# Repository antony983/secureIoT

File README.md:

# secureIoT
sample secureIOT design

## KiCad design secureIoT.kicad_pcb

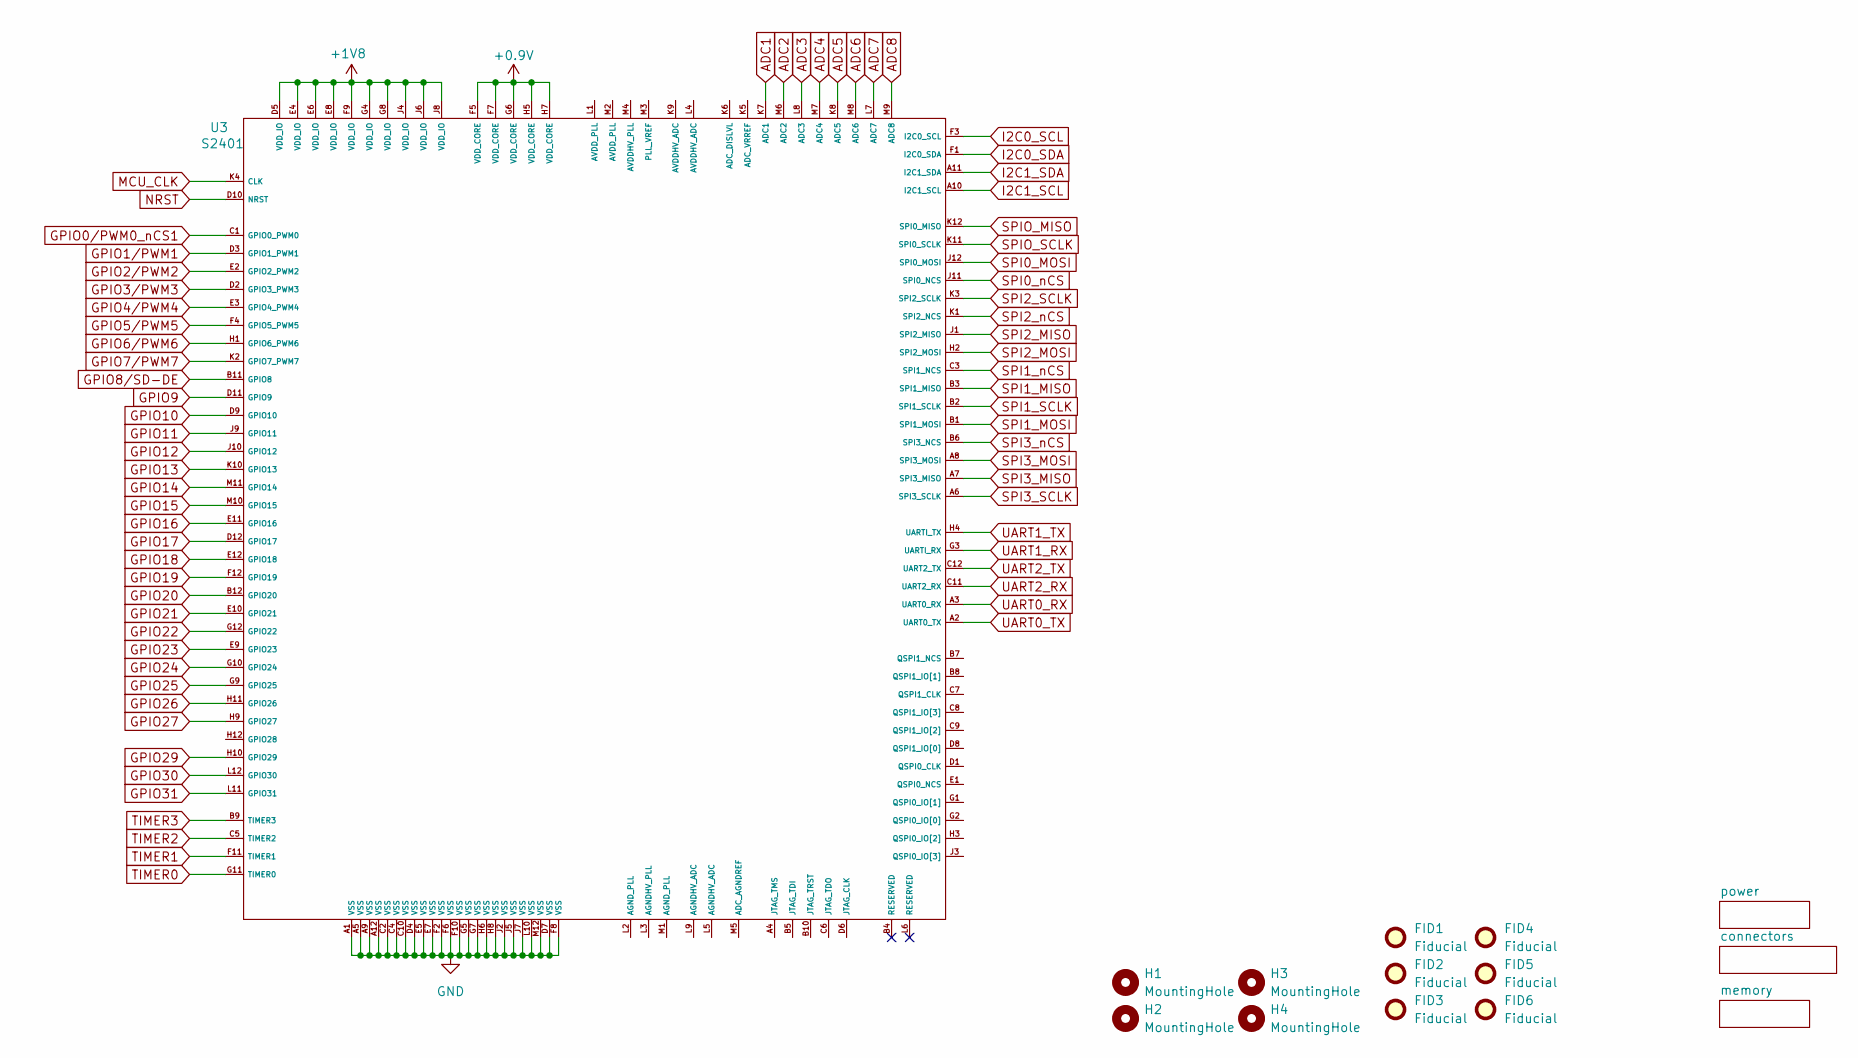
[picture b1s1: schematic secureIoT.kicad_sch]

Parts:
FID1, FID2, FID3, FID4, FID5, FID6: Fiducial; Fiducial_0.5mm_Mask1mm
H1, H2, H3, H4: MountingHole; MountingHole_3.5mm
U3: S2401; S4201

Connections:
+0.9V: U3.F5 (VDD_CORE), U3.F7 (VDD_CORE), U3.G6 (VDD_CORE), U3.H5 (VDD_CORE), U3.H7 (VDD_CORE); also elsewhere on the board
+1V8: U3.D5 (VDD_IO), U3.E4 (VDD_IO), U3.E6 (VDD_IO), U3.E8 (VDD_IO), U3.F9 (VDD_IO), U3.G4 (VDD_IO), U3.G8 (VDD_IO), U3.J4 (VDD_IO), U3.J6 (VDD_IO), U3.J8 (VDD_IO); also elsewhere on the board
ADC1: U3.K7 (ADC1); also elsewhere on the board
ADC2: U3.M6 (ADC2); also elsewhere on the board
ADC3: U3.L8 (ADC3); also elsewhere on the board
ADC4: U3.M7 (ADC4); also elsewhere on the board
ADC5: U3.K8 (ADC5); also elsewhere on the board
ADC6: U3.M8 (ADC6); also elsewhere on the board
ADC7: U3.L7 (ADC7); also elsewhere on the board
ADC8: U3.M9 (ADC8); also elsewhere on the board
GND: U3.A1 (VSS), U3.A5 (VSS), U3.A9 (VSS), U3.A12 (VSS), U3.C2 (VSS), U3.C4 (VSS), U3.C10 (VSS), U3.D4 (VSS), U3.D7 (VSS), U3.E5 (VSS), U3.E7 (VSS), U3.F2 (VSS), U3.F6 (VSS), U3.F8 (VSS), U3.F10 (VSS), U3.G5 (VSS), U3.G7 (VSS), U3.H6 (VSS), U3.H8 (VSS), U3.J2 (VSS), U3.J5 (VSS), U3.J7 (VSS), U3.L10 (VSS), U3.M12 (VSS); also elsewhere on the board
GPIO0/PWM0_nCS1: U3.C1 (GPIO0_PWM0); also elsewhere on the board
GPIO1/PWM1: U3.D3 (GPIO1_PWM1); also elsewhere on the board
GPIO2/PWM2: U3.E2 (GPIO2_PWM2); also elsewhere on the board
GPIO3/PWM3: U3.D2 (GPIO3_PWM3); also elsewhere on the board
GPIO4/PWM4: U3.E3 (GPIO4_PWM4); also elsewhere on the board
GPIO5/PWM5: U3.F4 (GPIO5_PWM5); also elsewhere on the board
GPIO6/PWM6: U3.H1 (GPIO6_PWM6); also elsewhere on the board
GPIO7/PWM7: U3.K2 (GPIO7_PWM7); also elsewhere on the board
GPIO8/SD-DE: U3.B11 (GPIO8); also elsewhere on the board
GPIO9: U3.D11 (GPIO9); also elsewhere on the board
GPIO10: U3.D9 (GPIO10); also elsewhere on the board
GPIO11: U3.J9 (GPIO11); also elsewhere on the board
GPIO12: U3.J10 (GPIO12); also elsewhere on the board
GPIO13: U3.K10 (GPIO13); also elsewhere on the board
GPIO14: U3.M11 (GPIO14); also elsewhere on the board
GPIO15: U3.M10 (GPIO15); also elsewhere on the board
GPIO16: U3.E11 (GPIO16); also elsewhere on the board
GPIO17: U3.D12 (GPIO17); also elsewhere on the board
GPIO18: U3.E12 (GPIO18); also elsewhere on the board
GPIO19: U3.F12 (GPIO19); also elsewhere on the board
GPIO20: U3.B12 (GPIO20); also elsewhere on the board
GPIO21: U3.E10 (GPIO21); also elsewhere on the board
GPIO22: U3.G12 (GPIO22); also elsewhere on the board
GPIO23: U3.E9 (GPIO23); also elsewhere on the board
GPIO24: U3.G10 (GPIO24); also elsewhere on the board
GPIO25: U3.G9 (GPIO25); also elsewhere on the board
GPIO26: U3.H11 (GPIO26); also elsewhere on the board
GPIO27: U3.H9 (GPIO27); also elsewhere on the board
GPIO29: U3.H10 (GPIO29); also elsewhere on the board
GPIO30: U3.L12 (GPIO30); also elsewhere on the board
GPIO31: U3.L11 (GPIO31); also elsewhere on the board
I2C0_SCL: U3.F3 (I2C0_SCL); also elsewhere on the board
I2C0_SDA: U3.F1 (I2C0_SDA); also elsewhere on the board
I2C1_SCL: U3.A10 (I2C1_SCL); also elsewhere on the board
I2C1_SDA: U3.A11 (I2C1_SDA); also elsewhere on the board
MCU_CLK: U3.K4 (CLK); also elsewhere on the board
NRST: U3.D10 (NRST); also elsewhere on the board
SPI0_MOSI: U3.J12 (SPI0_MOSI); also elsewhere on the board
SPI0_nCS: U3.J11 (SPI0_NCS); also elsewhere on the board
SPI1_MISO: U3.B3 (SPI1_MISO); also elsewhere on the board
SPI1_MOSI: U3.B1 (SPI1_MOSI); also elsewhere on the board
SPI1_SCLK: U3.B2 (SPI1_SCLK); also elsewhere on the board
SPI1_nCS: U3.C3 (SPI1_NCS); also elsewhere on the board
SPI2_MISO: U3.J1 (SPI2_MISO); also elsewhere on the board
SPI2_MOSI: U3.H2 (SPI2_MOSI); also elsewhere on the board
SPI2_SCLK: U3.K3 (SPI2_SCLK); also elsewhere on the board
SPI2_nCS: U3.K1 (SPI2_NCS); also elsewhere on the board
SPI3_MISO: U3.A7 (SPI3_MISO); also elsewhere on the board
SPI3_MOSI: U3.A8 (SPI3_MOSI); also elsewhere on the board
SPI3_SCLK: U3.A6 (SPI3_SCLK); also elsewhere on the board
SPI3_nCS: U3.B6 (SPI3_NCS); also elsewhere on the board
SPIO_MISO: U3.K12 (SPI0_MISO); also elsewhere on the board
SPIO_SCLK: U3.K11 (SPI0_SCLK); also elsewhere on the board
TIMER0: U3.G11 (TIMER0); also elsewhere on the board
TIMER1: U3.F11 (TIMER1); also elsewhere on the board
TIMER2: U3.C5 (TIMER2); also elsewhere on the board
TIMER3: U3.B9 (TIMER3); also elsewhere on the board
UART0_RX: U3.A3 (UART0_RX); also elsewhere on the board
UART0_TX: U3.A2 (UART0_TX); also elsewhere on the board
UART1_RX: U3.G3 (UARTI_RX); also elsewhere on the board
UART1_TX: U3.H4 (UARTI_TX); also elsewhere on the board
UART2_RX: U3.C11 (UART2_RX); also elsewhere on the board
UART2_TX: U3.C12 (UART2_TX); also elsewhere on the board

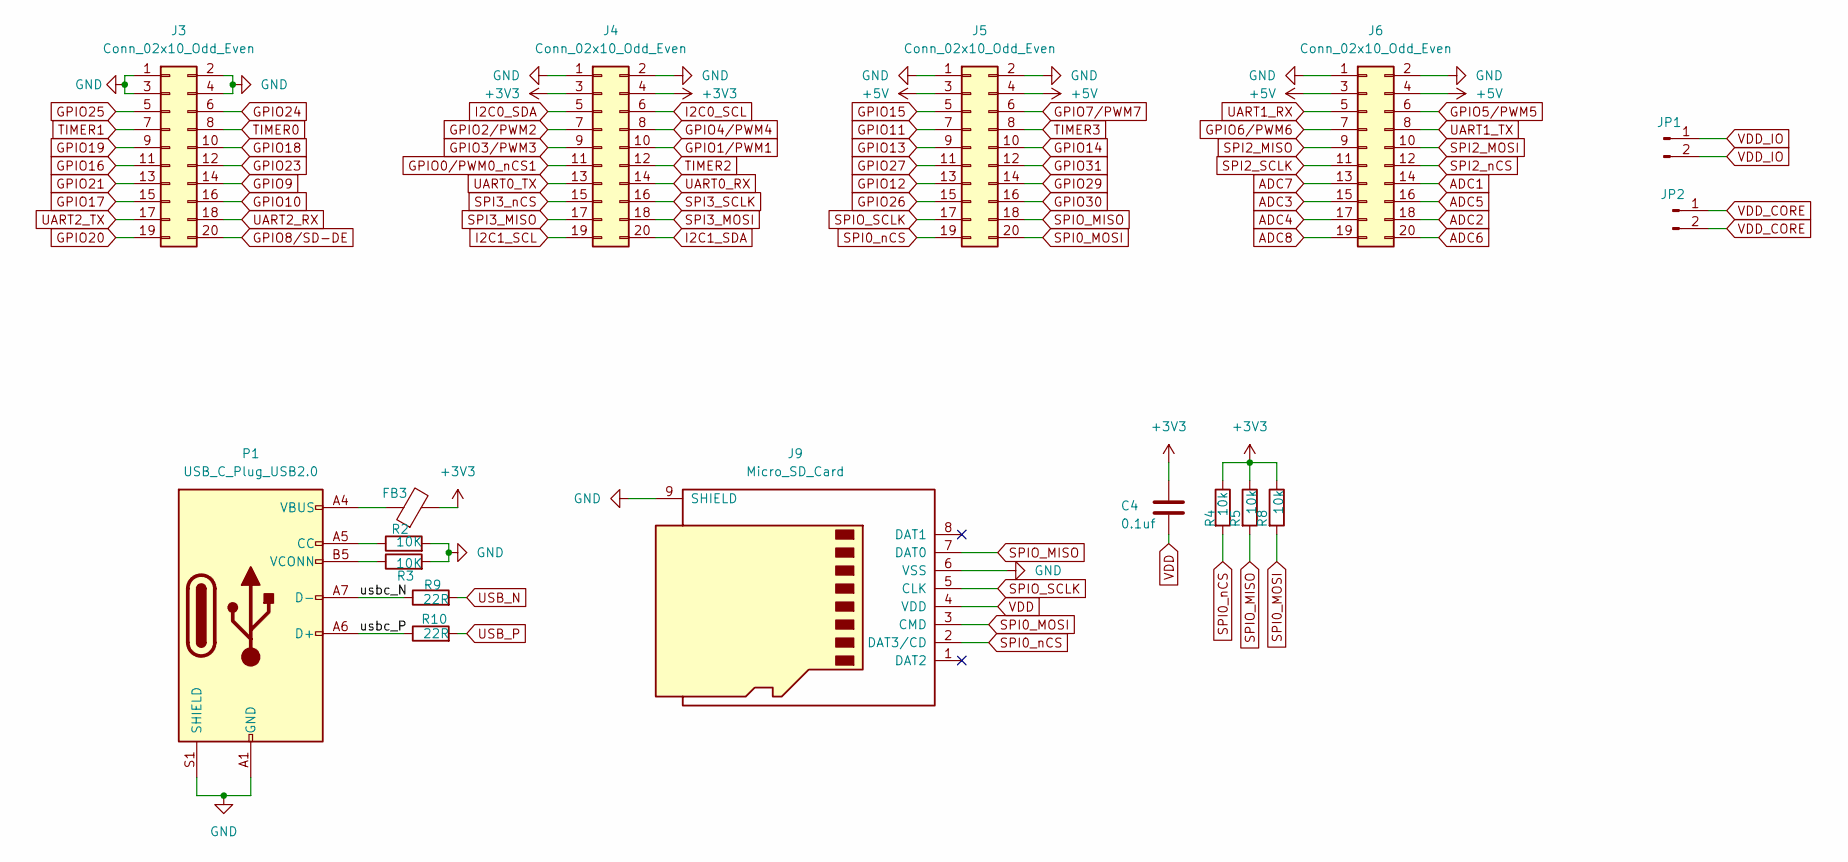
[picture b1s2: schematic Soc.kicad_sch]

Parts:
C4: 0.1uf; C_0603_1608Metric
FB3: FerriteBead; R_0603_1608Metric
J3, J4, J5, J6: Conn_02x10_Odd_Even; PinHeader_2x10_P2.54mm_Vertical
J9: Micro_SD_Card; microSD_HC_Molex_104031-0811
JP1, JP2: Conn_01x02_Pin; PinHeader_1x02_P2.54mm_Vertical
P1: USB_C_Plug_USB2.0; USB_C_Receptacle_GCT_USB4105-xx-A_16P_TopMnt_Horizontal
R2, R3: 10K; R_0603_1608Metric
R4, R5, R8: 10k; R_0603_1608Metric
R9, R10: 22R; R_0603_1608Metric

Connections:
+3V3: C4.1, FB3.2, J4.3, J4.4, R4.1, R5.1, R8.1; also elsewhere on the board
+5V: J5.3, J5.4, J6.3, J6.4; also elsewhere on the board
/connectors/usbc_N: P1.A7 (D-), R9.1
/connectors/usbc_P: P1.A6 (D+), R10.1
ADC1: J6.14; also elsewhere on the board
ADC2: J6.18; also elsewhere on the board
ADC3: J6.15; also elsewhere on the board
ADC4: J6.17; also elsewhere on the board
ADC5: J6.16; also elsewhere on the board
ADC6: J6.20; also elsewhere on the board
ADC7: J6.13; also elsewhere on the board
ADC8: J6.19; also elsewhere on the board
GND: J3.1, J3.2, J3.3, J3.4, J4.1, J4.2, J5.1, J5.2, J6.1, J6.2, J9.6 (VSS), J9.9 (SHIELD), P1.A1 (GND), P1.A12 (GND), P1.B1 (GND), P1.B12 (GND), P1.S1 (SHIELD), R2.2, R3.2; also elsewhere on the board
GPIO0/PWM0_nCS1: J4.11; also elsewhere on the board
GPIO1/PWM1: J4.10; also elsewhere on the board
GPIO2/PWM2: J4.7; also elsewhere on the board
GPIO3/PWM3: J4.9; also elsewhere on the board
GPIO4/PWM4: J4.8; also elsewhere on the board
GPIO5/PWM5: J6.6; also elsewhere on the board
GPIO6/PWM6: J6.7; also elsewhere on the board
GPIO7/PWM7: J5.6; also elsewhere on the board
GPIO8/SD-DE: J3.20; also elsewhere on the board
GPIO9: J3.14; also elsewhere on the board
GPIO10: J3.16; also elsewhere on the board
GPIO11: J5.7; also elsewhere on the board
GPIO12: J5.13; also elsewhere on the board
GPIO13: J5.9; also elsewhere on the board
GPIO14: J5.10; also elsewhere on the board
GPIO15: J5.5; also elsewhere on the board
GPIO16: J3.11; also elsewhere on the board
GPIO17: J3.15; also elsewhere on the board
GPIO18: J3.10; also elsewhere on the board
GPIO19: J3.9; also elsewhere on the board
GPIO20: J3.19; also elsewhere on the board
GPIO21: J3.13; also elsewhere on the board
GPIO23: J3.12; also elsewhere on the board
GPIO24: J3.6; also elsewhere on the board
GPIO25: J3.5; also elsewhere on the board
GPIO26: J5.15; also elsewhere on the board
GPIO27: J5.11; also elsewhere on the board
GPIO29: J5.14; also elsewhere on the board
GPIO30: J5.16; also elsewhere on the board
GPIO31: J5.12; also elsewhere on the board
I2C0_SCL: J4.6; also elsewhere on the board
I2C0_SDA: J4.5; also elsewhere on the board
I2C1_SCL: J4.19; also elsewhere on the board
I2C1_SDA: J4.20; also elsewhere on the board
unnamed: FB3.1, P1.A4 (VBUS), P1.A9 (VBUS), P1.B4 (VBUS), P1.B9 (VBUS)
unnamed: P1.A5 (CC), R2.1
unnamed: P1.B5 (VCONN), R3.1
SPI0_MOSI: J5.20, J9.3 (CMD), R8.2; also elsewhere on the board
SPI0_nCS: J5.19, J9.2 (DAT3/CD), R4.2; also elsewhere on the board
SPI2_MISO: J6.9; also elsewhere on the board
SPI2_MOSI: J6.10; also elsewhere on the board
SPI2_SCLK: J6.11; also elsewhere on the board
SPI2_nCS: J6.12; also elsewhere on the board
SPI3_MISO: J4.17; also elsewhere on the board
SPI3_MOSI: J4.18; also elsewhere on the board
SPI3_SCLK: J4.16; also elsewhere on the board
SPI3_nCS: J4.15; also elsewhere on the board
SPIO_MISO: J5.18, J9.7 (DAT0), R5.2; also elsewhere on the board
SPIO_SCLK: J5.17, J9.5 (CLK); also elsewhere on the board
TIMER0: J3.8; also elsewhere on the board
TIMER1: J3.7; also elsewhere on the board
TIMER2: J4.12; also elsewhere on the board
TIMER3: J5.8; also elsewhere on the board
UART0_RX: J4.14; also elsewhere on the board
UART0_TX: J4.13; also elsewhere on the board
UART1_RX: J6.5; also elsewhere on the board
UART1_TX: J6.8; also elsewhere on the board
UART2_RX: J3.18; also elsewhere on the board
UART2_TX: J3.17; also elsewhere on the board
USB_N: R9.2; also elsewhere on the board
USB_P: R10.2; also elsewhere on the board
VDD: C4.2, J9.4 (VDD)
VDD_CORE: JP2.1, JP2.2
VDD_IO: JP1.1, JP1.2

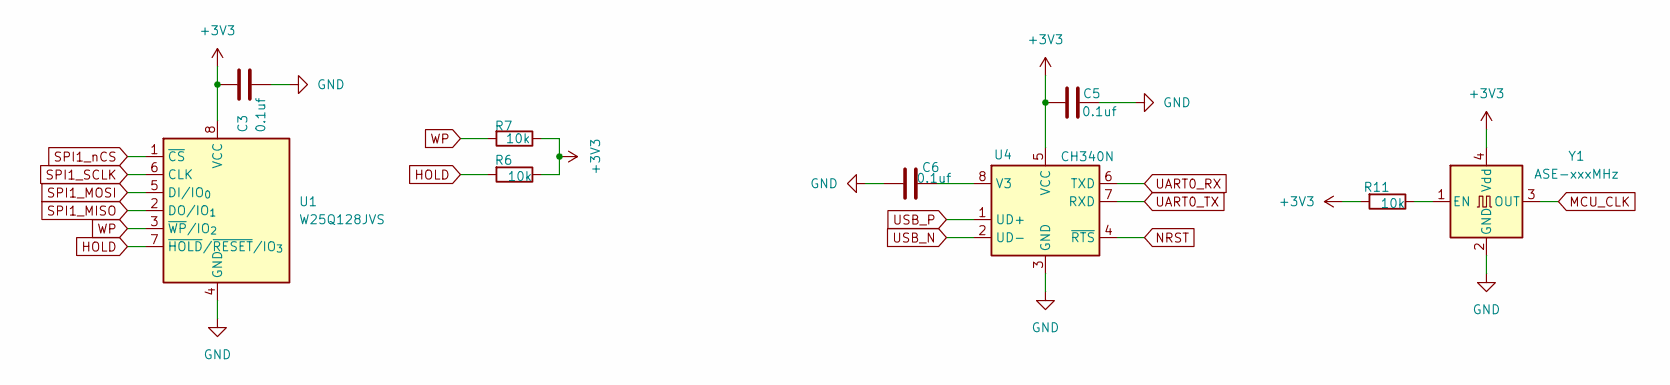
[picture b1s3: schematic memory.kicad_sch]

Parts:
C3, C5, C6: 0.1uf; C_0603_1608Metric
R6, R7, R11: 10k; R_0603_1608Metric
U1: W25Q128JVS; SOIC-8_5.3x5.3mm_P1.27mm
U4: CH340N; JEITA_SOIC-8_3.9x4.9mm_P1.27mm
Y1: ASE-xxxMHz; Oscillator_SMD_Abracon_ASE-4Pin_3.2x2.5mm

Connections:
+3V3: C3.1, C5.1, R6.1, R7.1, R11.2, U1.8 (VCC), U4.5 (VCC), Y1.4 (Vdd); also elsewhere on the board
GND: C3.2, C5.2, C6.2, U1.4 (GND), U4.3 (GND), Y1.2 (GND); also elsewhere on the board
HOLD: R6.2, U1.7 (~HOLD/~RESET/IO_{3})
MCU_CLK: Y1.3 (OUT); also elsewhere on the board
NRST: U4.4 (~RTS); also elsewhere on the board
unnamed: C6.1, U4.8 (V3)
unnamed: R11.1, Y1.1 (EN)
SPI1_MISO: U1.2 (DO/IO_{1}); also elsewhere on the board
SPI1_MOSI: U1.5 (DI/IO_{0}); also elsewhere on the board
SPI1_SCLK: U1.6 (CLK); also elsewhere on the board
SPI1_nCS: U1.1 (~CS); also elsewhere on the board
UART0_RX: U4.6 (TXD); also elsewhere on the board
UART0_TX: U4.7 (RXD); also elsewhere on the board
USB_N: U4.2 (UD-); also elsewhere on the board
USB_P: U4.1 (UD+); also elsewhere on the board
WP: R7.2, U1.3 (~WP/IO_{2})

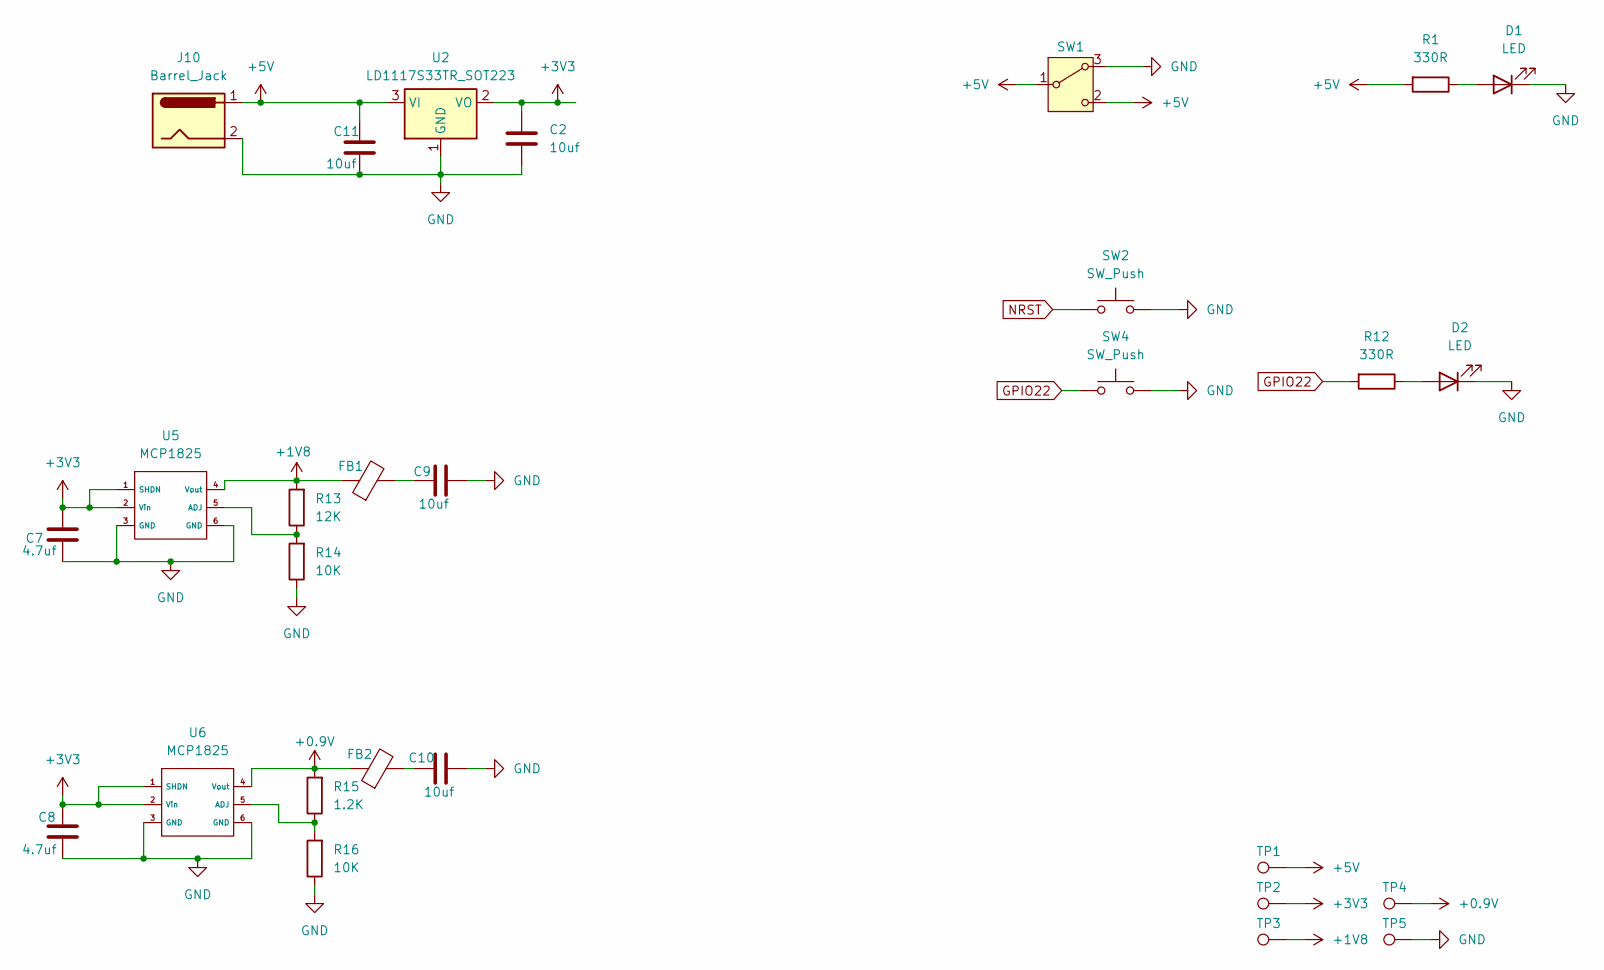
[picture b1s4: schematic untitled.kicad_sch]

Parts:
C2, C11: 10uf; CP_EIA-2012-12_Kemet-R
C7, C8: 4.7uf; C_0603_1608Metric
C9, C10: 10uf; C_0603_1608Metric
D1, D2: LED; LED_0603_1608Metric
FB1, FB2: FerriteBead; R_0603_1608Metric
J10: Barrel_Jack; BarrelJack_GCT_DCJ200-10-A_Horizontal
R1: 330R; R_0603_1608Metric
R12: 330R; LED_0603_1608Metric
R13: 12K; R_0603_1608Metric
R14, R16: 10K; R_0603_1608Metric
R15: 1.2K; R_0603_1608Metric
SW1: SW_Wuerth_450301014042; SW_Slide-03_Wuerth-WS-SLTV_10x2.5x6.4_P2.54mm
SW2, SW4: SW_Push; SW_Push_1P1T-SH_NO_CK_KMR2xxG
TP1, TP2, TP3, TP4, TP5: TestPoint; TestPoint_Loop_D2.54mm_Drill1.5mm_Beaded
U2: LD1117S33TR_SOT223; SOT-223-3_TabPin2
U5, U6: MCP1825

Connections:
+0.9V: FB2.1, R15.2, TP4.1, U6.4 (Vout); also elsewhere on the board
+1V8: FB1.1, R13.2, TP3.1, U5.4 (Vout); also elsewhere on the board
+3V3: C2.1, C7.1, C8.1, TP2.1, U2.2 (VO), U5.1 (SHDN), U5.2 (Vin), U6.1 (SHDN), U6.2 (Vin); also elsewhere on the board
+5V: C11.1, J10.1, R1.2, SW1.1 (B), SW1.2 (C), TP1.1, U2.3 (VI); also elsewhere on the board
GND: C2.2, C7.2, C8.2, C9.2, C10.2, C11.2, D1.1 (K), D2.1 (K), J10.2, R14.1, R16.1, SW1.3 (A), SW2.2, SW4.2, TP5.1, U2.1 (GND), U5.3 (GND), U5.6 (GND), U6.3 (GND), U6.6 (GND); also elsewhere on the board
GPIO22: R12.2, SW4.1; also elsewhere on the board
NRST: SW2.1; also elsewhere on the board
unnamed: C9.1, FB1.2
unnamed: C10.1, FB2.2
unnamed: D1.2 (A), R1.1
unnamed: D2.2 (A), R12.1
unnamed: R13.1, R14.2, U5.5 (ADJ)
unnamed: R15.1, R16.2, U6.5 (ADJ)

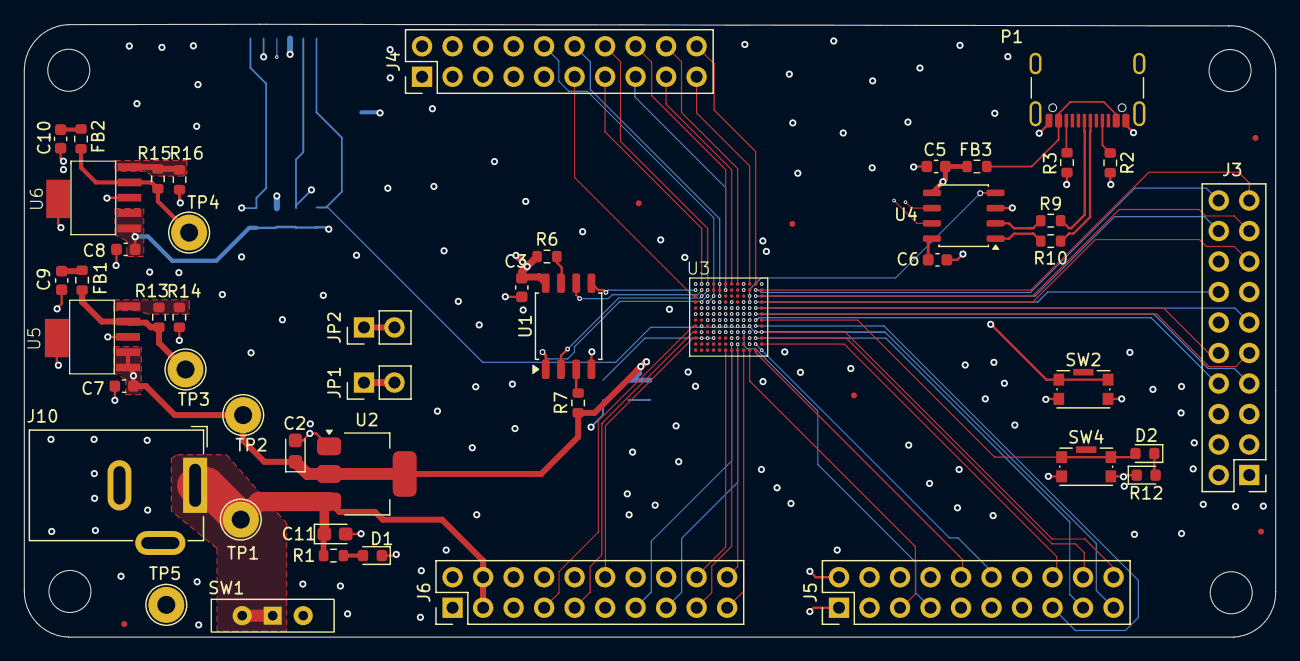
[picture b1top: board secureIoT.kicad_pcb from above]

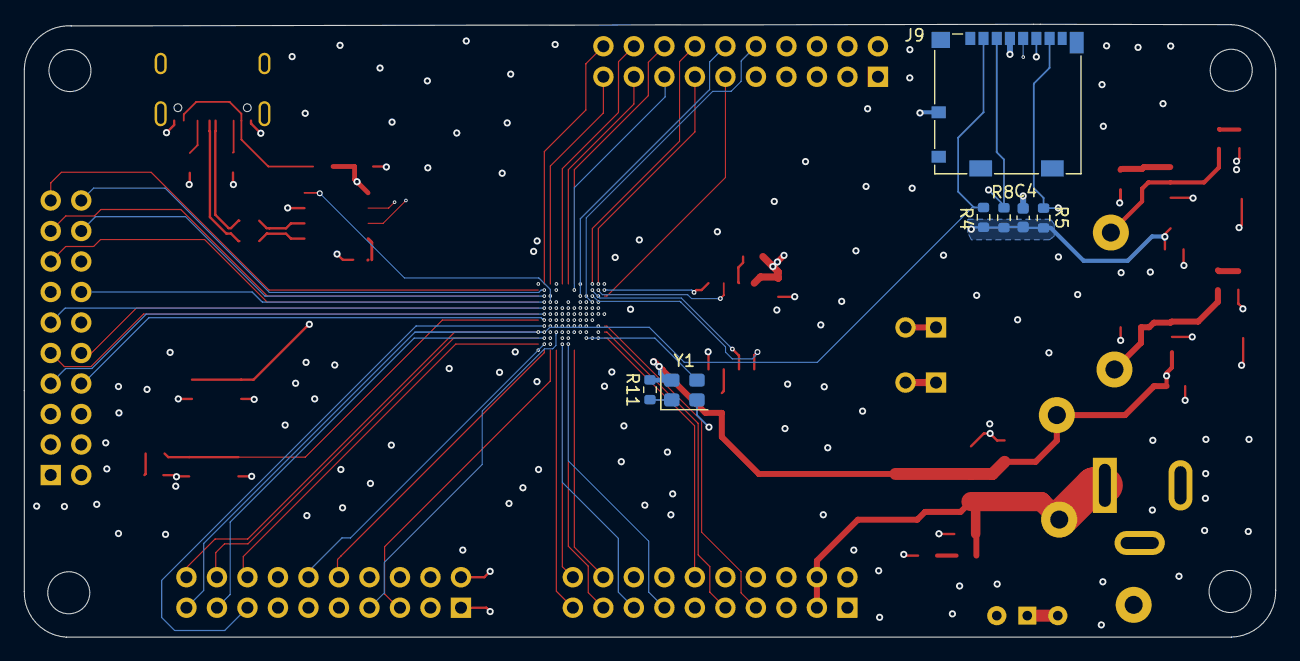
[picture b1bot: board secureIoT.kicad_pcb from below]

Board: 6 copper layers, 104.2 x 51.0 mm, 65 parts (7 on the bottom side), 96 nets.
